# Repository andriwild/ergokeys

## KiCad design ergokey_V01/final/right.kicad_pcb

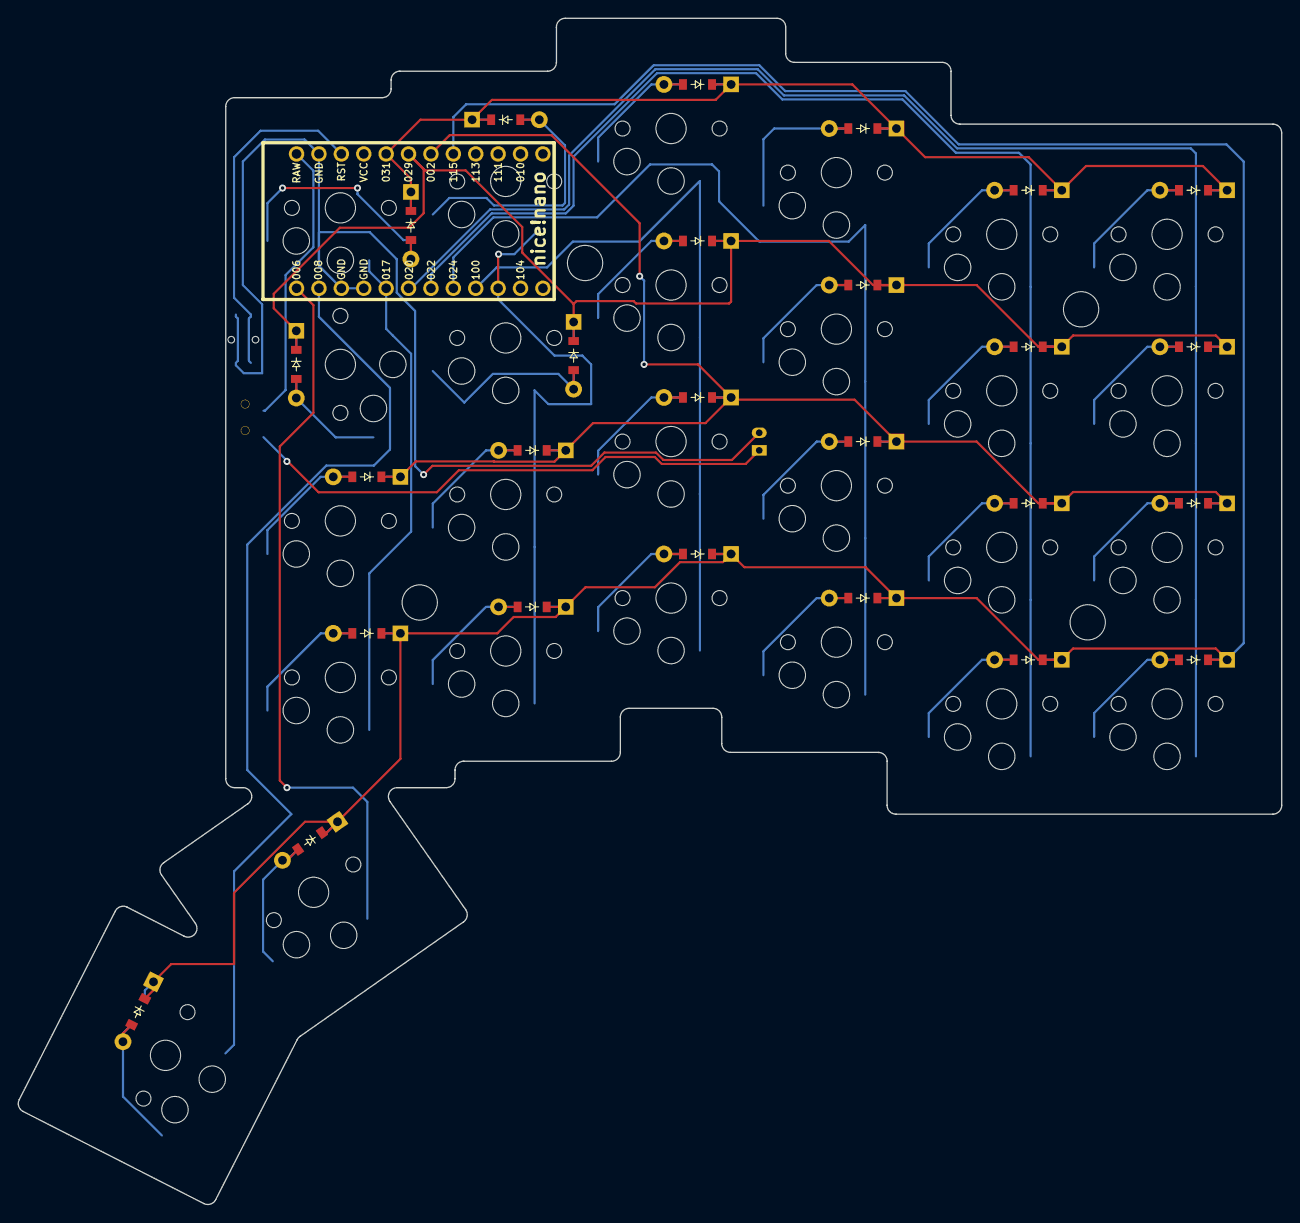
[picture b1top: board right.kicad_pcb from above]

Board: 2 copper layers, 143.3 x 134.5 mm, 56 parts (0 on the bottom side), 42 nets.

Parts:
B1: Panasonic_EVQPUL_EVQPUC
D1, D2, D3, D4, D5, D6, D7, D8, D9, D10, D11, D12, D13, D14, D15, D16, D17, D18, D19, D20, D21, D22, D23, D24, D25, D26: ComboDiode
JST1: JST_PH_S2B-PH-K_02x2.00mm_Angled
MCU1: nice_nano
S1, S2, S3, S4, S5, S6, S7, S8, S9, S10, S11, S12, S13, S14, S15, S16, S17, S18, S19, S20, S21, S22, S23, S24, S25, S26: PG1350
T1: SPDT_C128955

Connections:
GND: B1.1, JST1.2, MCU1.3, MCU1.4, MCU1.23
P002: D2.1, D6.1, D10.1, D14.1, D18.1, D20.1, MCU1.18
P006: MCU1.1, S24.1
P008: MCU1.2, S25.1
P011: MCU1.10, S17.1, S18.1, S19.1, S20.1
P017: MCU1.5, S21.1, S22.1, S23.1, S26.1
P020: MCU1.6, S1.1, S2.1, S3.1, S4.1
P022: MCU1.7, S5.1, S6.1, S7.1, S8.1
P024: MCU1.8, S9.1, S10.1, S11.1, S12.1
P029: D3.1, D7.1, D11.1, D15.1, D25.1, D26.1, MCU1.19
P031: D4.1, D8.1, D12.1, D16.1, D23.1, D24.1, MCU1.20
P100: MCU1.9, S13.1, S14.1, S15.1, S16.1
P115: D1.1, D5.1, D9.1, D13.1, D17.1, D19.1, D21.1, D22.1, MCU1.17
RAW: MCU1.24, T1.2
RST: B1.2, MCU1.22
mirror_far_default: D22.2, S25.2
mirror_fifth_bottom: D17.2, S17.2
mirror_fifth_home: D18.2, S18.2
mirror_fifth_num: D24.2, S20.2
mirror_fifth_top: D25.2, S19.2
mirror_first_bottom: D1.2, S1.2
mirror_first_home: D2.2, S2.2
mirror_first_num: D4.2, S4.2
mirror_first_top: D3.2, S3.2
mirror_fourth_bottom: D13.2, S13.2
mirror_fourth_home: D14.2, S14.2
mirror_fourth_num: D16.2, S16.2
mirror_fourth_top: D15.2, S15.2
mirror_home_default: D21.2, S24.2
mirror_second_bottom: D5.2, S5.2
mirror_second_home: D6.2, S6.2
mirror_second_num: D8.2, S8.2
mirror_second_top: D7.2, S7.2
mirror_sixth_bottom: D19.2, S21.2
mirror_sixth_home: D20.2, S22.2
mirror_sixth_num: D23.2, S23.2
mirror_sixth_top: D26.2, S26.2
mirror_third_bottom: D9.2, S9.2
mirror_third_home: D10.2, S10.2
mirror_third_num: D12.2, S12.2
mirror_third_top: D11.2, S11.2
pos: JST1.1, T1.1

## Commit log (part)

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2024-10-23 add right hand side
2024-10-23 remove nice_nano confilicting holes
2024-10-28 reposition diodes of right side
2024-10-28 remove conflicting holes
2025-01-04 add generated files
